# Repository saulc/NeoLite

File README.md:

# NeoLite
 neopixel wrapper class with no delay animations.

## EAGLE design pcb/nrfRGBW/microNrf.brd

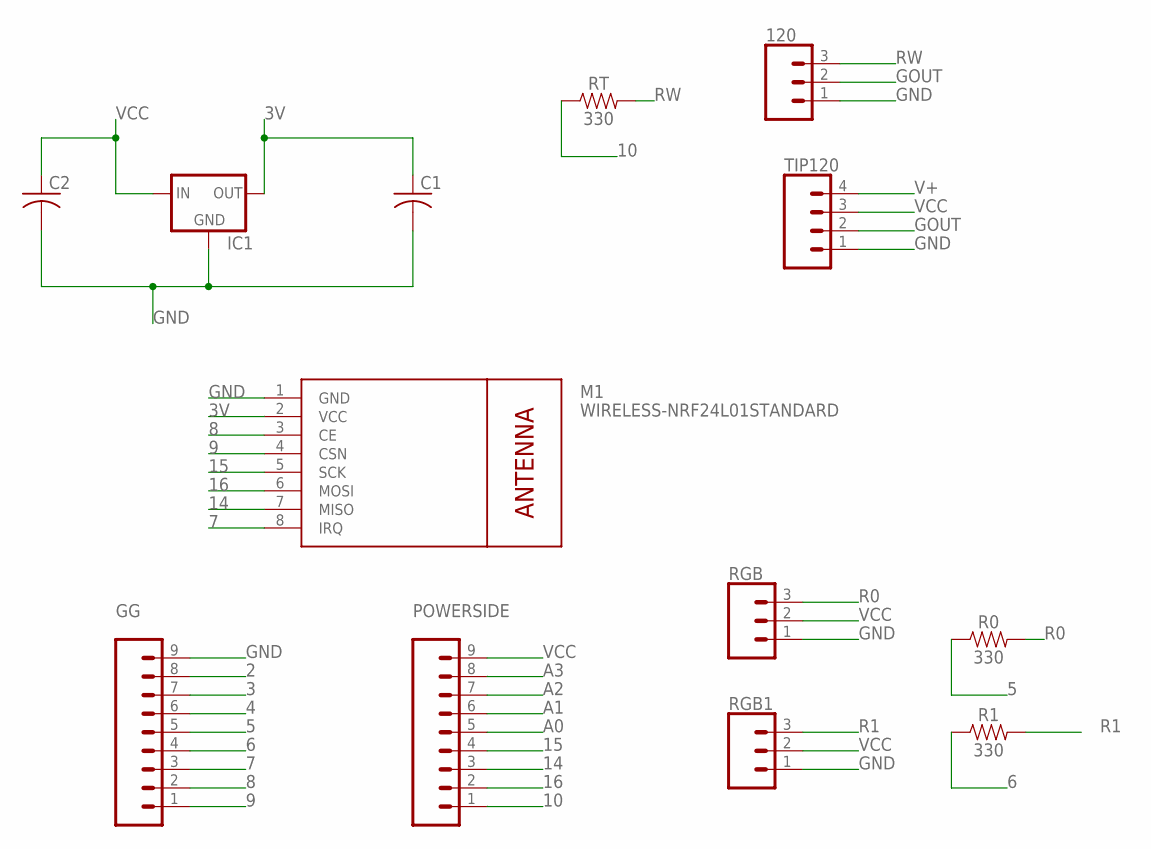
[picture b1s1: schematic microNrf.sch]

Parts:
120: CONN_03LONGPADS; 1X03_LONGPADS
C1, C2: C-US025-030X050; C025-030X050
GG: CONN_09; 1X09
IC1: MCP1700TRI; TO92
M1: WIRELESS-NRF24L01STANDARD; WIRELESS-NRF24L01
POWERSIDE: CONN_09; 1X09
R0, R1: 330; 0603
RGB, RGB1: CONN_03LONGPADS; 1X03_LONGPADS
RT: 330; 0603
TIP120: CONN_04LONGPADS; 1X04_LONGPADS

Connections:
2: GG.8
3: GG.7
3V: C1.1, IC1.3 (OUT), M1.2 (VCC)
4: GG.6
5: GG.5, R0.1
6: GG.4, R1.1
7: GG.3, M1.8 (IRQ)
8: GG.2, M1.3 (CE)
9: GG.1, M1.4 (CSN)
10: POWERSIDE.1, RT.1
14: M1.7 (MISO), POWERSIDE.3
15: M1.5 (SCK), POWERSIDE.4
16: M1.6 (MOSI), POWERSIDE.2
A0: POWERSIDE.5
A1: POWERSIDE.6
A2: POWERSIDE.7
A3: POWERSIDE.8
GND: 120.1, C1.2, C2.2, GG.9, IC1.1 (GND), M1.1 (GND), RGB.1, RGB1.1, TIP120.1
GOUT: 120.2, TIP120.2
R0: R0.2, RGB.3
R1: R1.2, RGB1.3
RW: 120.3, RT.2
V+: TIP120.4
VCC: C2.1, IC1.2 (IN), POWERSIDE.9, RGB.2, RGB1.2, TIP120.3

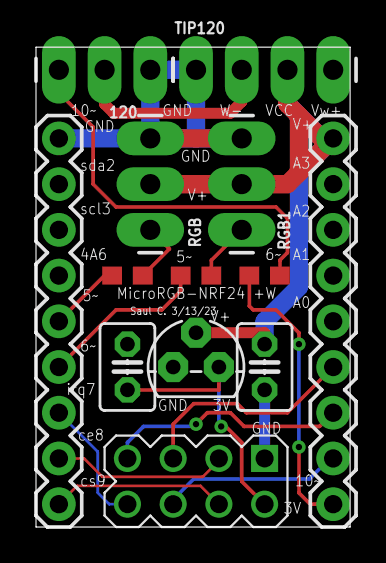
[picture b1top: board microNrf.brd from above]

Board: 2 copper layers, 17.4 x 26.7 mm, 13 parts (0 on the bottom side), 16 nets.

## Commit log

2022-10-02 ..
    ...
2022-10-05 pir
    motion detection sensor...interupt
2022-10-05 8bit
    ...
2022-10-08 new 2 button
    full control double taps...
2022-10-08 works.
    ...nice
2023-02-27 things
    ..
2023-03-13 idk
    making new ones work
2023-03-21 Rainbow Freeze
    bitbybit transistions for rcy...rbow..
    scroll/freeze mode ready...
    Need to update other version/convert to library
2023-04-14 ..
    ..
2024-03-05 pcb
    rgb + w
2024-03-05 pcb
    backup
2025-05-22 ...
    pir

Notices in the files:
parts and their libraries:
SparkFun-Connectors: Licensing: Creative Commons ShareAlike 4.0 International - https://creativecommons.org/licenses/by-sa/4.0
